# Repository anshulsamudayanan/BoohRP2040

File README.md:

# Booh RP2040

A minimal, RP2040-based Pi Pico clone, designed and built from scratch in KiCad.

## Overview

Booh RP2040 is a custom development board built around the Raspberry Pi RP2040 microcontroller.This repo covers schematic capture, PCB layout, and assembly for a minimal Pico-style board.

## Specs

- **MCU:** Raspberry Pi RP204
- **Flash:** W25Q16JV, 2MB QSPI flash
- **Power:** USB-C input, regulated to 3.3V via onboard LDO
- **I/O:** through-hole pin headers along both edges
- **Layout:** 2-layer PCB with groud layer
- **Form factor:** Pi Pico-sized footprint

## Repo Contents

- `kicad/` — KiCad schematic and PCB layout files
- `gerbers/` — Gerber files for manufacturing
- `bom/` — Bill of materials

## Getting Started

1. Order the PCB using the Gerber files in `gerbers/` (JLCPCB, PCBWay, etc.)
2. Source components using the BOM in `bom/`
3. Assemble and Solder by hand to obtain new skillz
4. Flash with MicroPython, CircuitPython, or the Pico SDK like a standard RP2040 board

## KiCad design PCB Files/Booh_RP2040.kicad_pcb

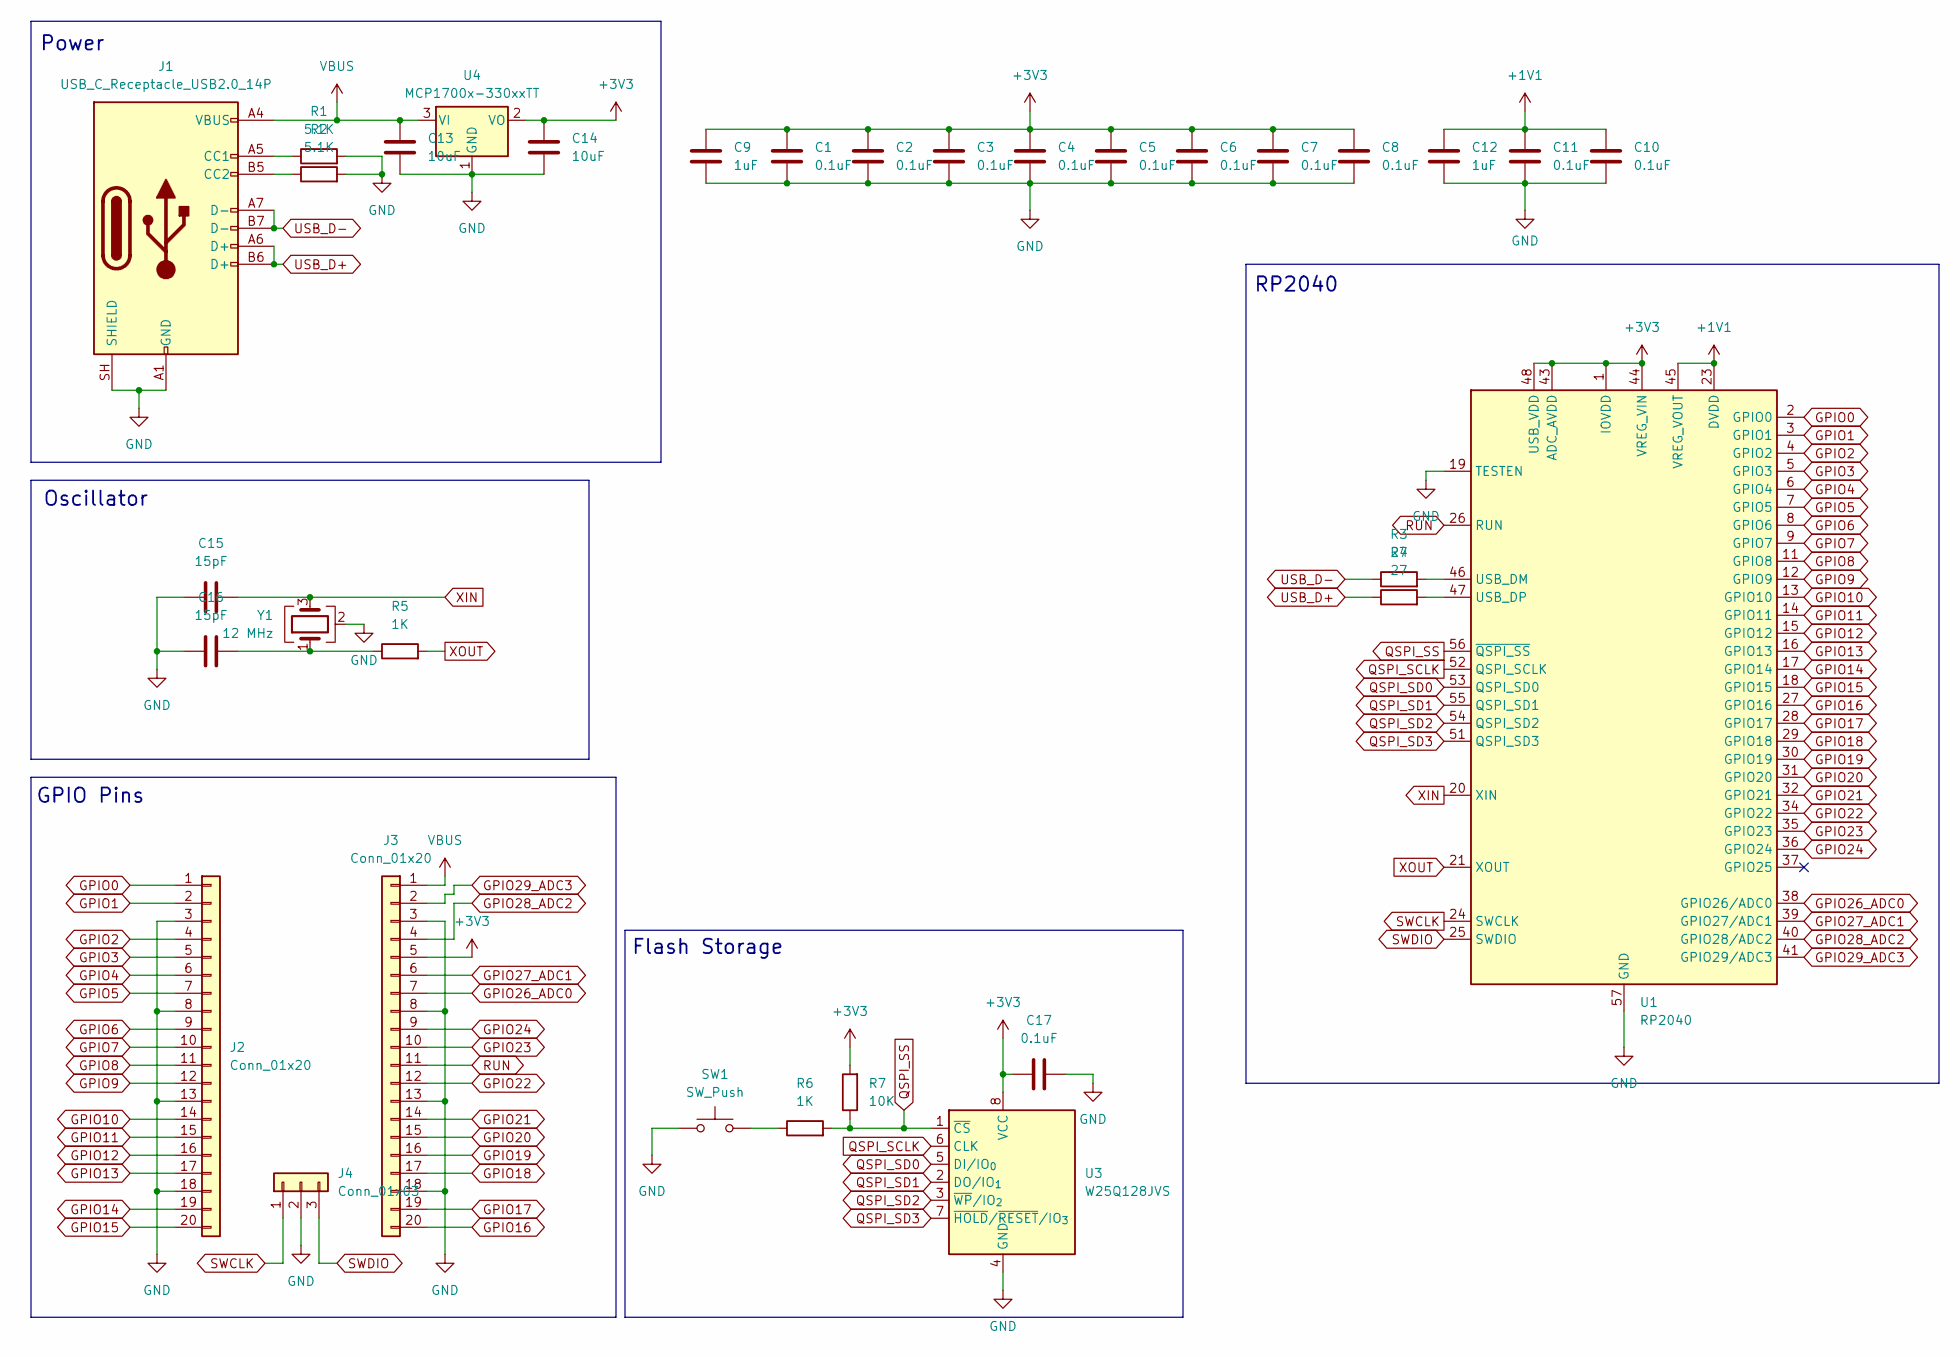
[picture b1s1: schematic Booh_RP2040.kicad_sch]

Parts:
C1, C2, C3, C4, C5, C6, C7, C8, C10, C11, C17: 0.1uF; C_0402_1005Metric
C9, C12: 1uF; C_0402_1005Metric
C13, C14: 10uF; C_0603_1608Metric
C15, C16: 15pF; C_0402_1005Metric
J1: USB_C_Receptacle_USB2.0_14P; USB_C_Receptacle_HRO_TYPE-C-31-M-12
J2, J3: Conn_01x20; PinHeader_1x20_P2.54mm_Vertical
J4: Conn_01x03; PinHeader_1x03_P2.54mm_Vertical
R1, R2: 5.1K; R_0402_1005Metric
R3, R4: 27; R_0402_1005Metric
R5, R6: 1K; R_0402_1005Metric
R7: 10K; R_0402_1005Metric
SW1: SW_Push; SW_Push_SPST_NO_Alps_SKRK
U1: RP2040; QFN-56-1EP_7x7mm_P0.4mm_EP3.2x3.2mm
U3: W25Q128JVS; Winbond_USON-8-1EP_3x2mm_P0.5mm_EP0.2x1.6mm
U4: MCP1700x-330xxTT; SOT-23
Y1: 12 MHz; Crystal_SMD_3225-4Pin_3.2x2.5mm

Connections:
+1V1: C10.1, C11.1, C12.1, U1.23 (DVDD), U1.45 (VREG_VOUT), U1.50 (DVDD)
+3V3: C1.1, C2.1, C3.1, C4.1, C5.1, C6.1, C7.1, C8.1, C9.1, C14.1, C17.1, J3.5, R7.2, U1.1 (IOVDD), U1.10 (IOVDD), U1.22 (IOVDD), U1.33 (IOVDD), U1.42 (IOVDD), U1.43 (ADC_AVDD), U1.44 (VREG_VIN), U1.48 (USB_VDD), U1.49 (IOVDD), U3.8 (VCC), U4.2 (VO)
GND: C1.2, C2.2, C3.2, C4.2, C5.2, C6.2, C7.2, C8.2, C9.2, C10.2, C11.2, C12.2, C13.2, C14.2, C15.1, C16.1, C17.2, J1.A1 (GND), J1.A12 (GND), J1.B1 (GND), J1.B12 (GND), J1.SH (SHIELD), J2.3, J2.8, J2.13, J2.18, J3.3, J3.8, J3.13, J3.18, J4.2, R1.2, R2.2, SW1.1, U1.19 (TESTEN), U1.57 (GND), U3.4 (GND), U4.1 (GND), Y1.2 (G), Y1.4 (G)
GPIO0: J2.1, U1.2 (GPIO0)
GPIO1: J2.2, U1.3 (GPIO1)
GPIO2: J2.4, U1.4 (GPIO2)
GPIO3: J2.5, U1.5 (GPIO3)
GPIO4: J2.6, U1.6 (GPIO4)
GPIO5: J2.7, U1.7 (GPIO5)
GPIO6: J2.9, U1.8 (GPIO6)
GPIO7: J2.10, U1.9 (GPIO7)
GPIO8: J2.11, U1.11 (GPIO8)
GPIO9: J2.12, U1.12 (GPIO9)
GPIO10: J2.14, U1.13 (GPIO10)
GPIO11: J2.15, U1.14 (GPIO11)
GPIO12: J2.16, U1.15 (GPIO12)
GPIO13: J2.17, U1.16 (GPIO13)
GPIO14: J2.19, U1.17 (GPIO14)
GPIO15: J2.20, U1.18 (GPIO15)
GPIO16: J3.20, U1.27 (GPIO16)
GPIO17: J3.19, U1.28 (GPIO17)
GPIO18: J3.17, U1.29 (GPIO18)
GPIO19: J3.16, U1.30 (GPIO19)
GPIO20: J3.15, U1.31 (GPIO20)
GPIO21: J3.14, U1.32 (GPIO21)
GPIO22: J3.12, U1.34 (GPIO22)
GPIO23: J3.10, U1.35 (GPIO23)
GPIO24: J3.9, U1.36 (GPIO24)
GPIO26_ADC0: J3.7, U1.38 (GPIO26/ADC0)
GPIO27_ADC1: J3.6, U1.39 (GPIO27/ADC1)
GPIO28_ADC2: J3.4, U1.40 (GPIO28/ADC2)
GPIO29_ADC3: J3.2, U1.41 (GPIO29/ADC3)
unnamed: C16.2, R5.1, Y1.1
unnamed: J1.A5 (CC1), R1.1
unnamed: J1.B5 (CC2), R2.1
unnamed: R6.1, SW1.2
unnamed: R3.2, U1.46 (USB_DM)
unnamed: R4.2, U1.47 (USB_DP)
QSPI_SCLK: U1.52 (QSPI_SCLK), U3.6 (CLK)
QSPI_SD0: U1.53 (QSPI_SD0), U3.5 (DI/IO_{0})
QSPI_SD1: U1.55 (QSPI_SD1), U3.2 (DO/IO_{1})
QSPI_SD2: U1.54 (QSPI_SD2), U3.3 (~WP/IO_{2})
QSPI_SD3: U1.51 (QSPI_SD3), U3.7 (~HOLD/~RESET/IO_{3})
QSPI_SS: R6.2, R7.1, U1.56 (~QSPI_SS), U3.1 (~CS)
RUN: J3.11, U1.26 (RUN)
SWCLK: J4.1, U1.24 (SWCLK)
SWDIO: J4.3, U1.25 (SWDIO)
USB_D+: J1.A6 (D+), J1.B6 (D+), R4.1
USB_D-: J1.A7 (D-), J1.B7 (D-), R3.1
VBUS: C13.1, J1.A4 (VBUS), J1.A9 (VBUS), J1.B4 (VBUS), J1.B9 (VBUS), J3.1, U4.3 (VI)
XIN: C15.2, U1.20 (XIN), Y1.3
XOUT: R5.2, U1.21 (XOUT)

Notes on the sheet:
Oscillator
GPIO Pins
RP2040
Flash Storage
Power

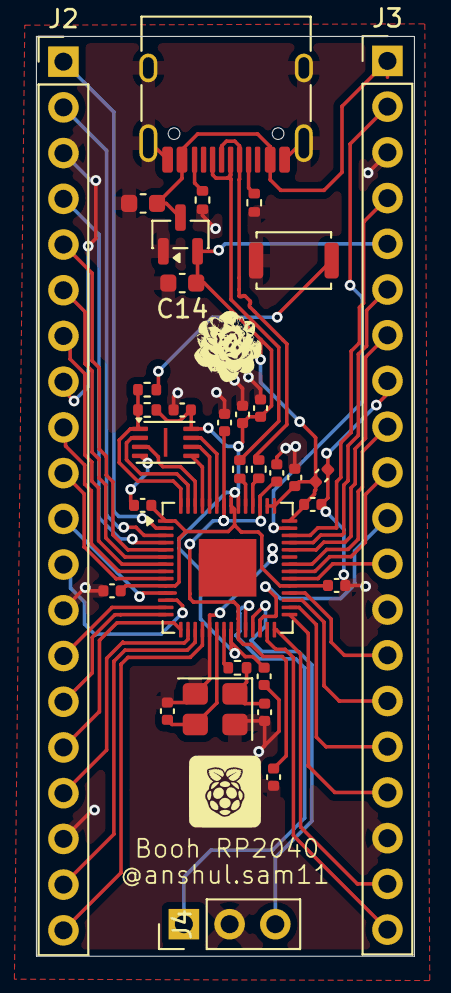
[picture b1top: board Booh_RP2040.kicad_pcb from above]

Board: 2 copper layers, 21.0 x 51.1 mm, 33 parts (0 on the bottom side), 52 nets.
